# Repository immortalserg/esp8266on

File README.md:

# esp8266on

http://xn--b1afas9b4a.xn--p1ai/archives/1248

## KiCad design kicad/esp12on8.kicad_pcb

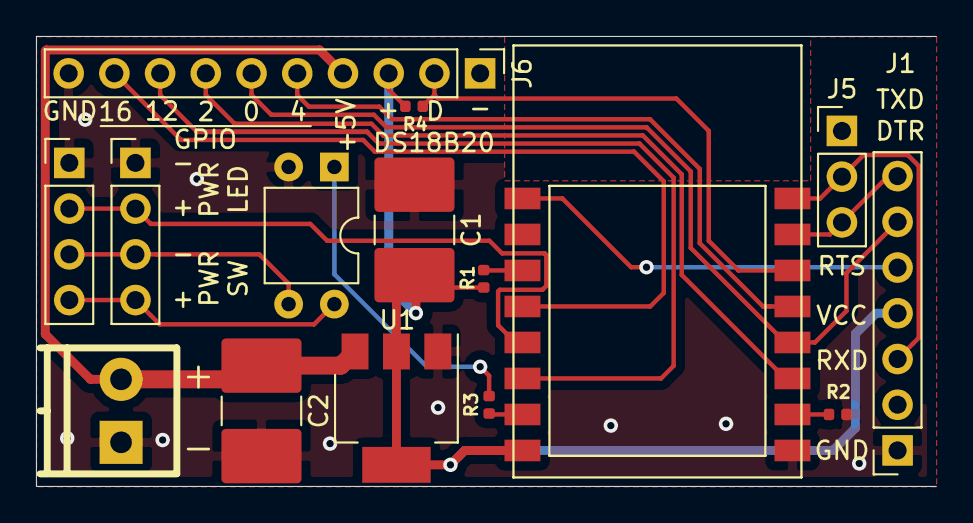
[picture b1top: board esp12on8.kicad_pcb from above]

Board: 2 copper layers, 50.0 x 25.0 mm, 15 parts (0 on the bottom side), 19 nets.

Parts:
C1, C2: CP; C_2816_7142Metric
J1: HEADER-1x07; PinSocket_1x07_P2.54mm_Vertical
J2: HEADER-1x02; pt_1,5-2-3,5-h
J3, J4: HEADER-1x04; PinHeader_1x04_P2.54mm_Vertical
J5: HEADER-1x03; PinHeader_1x03_P2.54mm_Vertical
J6: HEADER-1x10; PinHeader_1x10_P2.54mm_Vertical
R1, R2: 10 k; R_0402_1005Metric
R3: 1 k; R_0402_1005Metric
R4: 4.7 k; R_0402_1005Metric
U1: LM1117-3.3; SOT-223-3_TabPin2
U2: ESP-12
U3: EL814; DIP-4_W7.62mm

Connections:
+3.3V: C1.1, J1.4, J6.3, R1.1, R4.1, U1.2, U2.8
+5V: C2.1, J2.2, J6.4, U1.3
GND: C1.2, C2.2, J1.1, J2.1, J3.1, J4.1, J6.1, J6.10, R2.2, U1.1, U2.9, U3.2
unnamed: J1.3, J5.2, U2.16
unnamed: J1.5, U2.1
unnamed: J1.6, J6.6, U2.12
unnamed: J1.7, J5.3, U2.15
unnamed: J3.2, J4.2, U2.5
unnamed: J3.3, J4.3, U3.3
unnamed: J3.4, J4.4, U3.4
unnamed: J6.2, R4.2, U2.14
unnamed: J6.5, U2.13
unnamed: J6.7, U2.11
unnamed: J6.8, U2.6
unnamed: J6.9, U2.4
unnamed: R1.2, U2.3
unnamed: R2.1, U2.10
unnamed: R3.1, U2.7
unnamed: R3.2, U3.1

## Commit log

2019-01-22 a msg
